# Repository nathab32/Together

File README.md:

# Together

## About

Together is a device for maintaining connections with friends and companions. Together is heavily inspired by Tamagotchi devices, but differs in that it is collaborative. Born from a graduating senior in need of grad gift ideas, Together hopes to allow friends to stay connected even after they are physically separated.

## Planned Features

- Record voice notes for friends or personal use
- Playback voice notes with integrated speaker
- Start streaks with your friends
- Addressible RGBs to see status of friends/do whatever you want
- Complete tasks with your companions to grow pets!
- Use as microphone for computer/phone or bluetooth speaker
- Tuner
- Metronome

ESP32-D0WD-V3

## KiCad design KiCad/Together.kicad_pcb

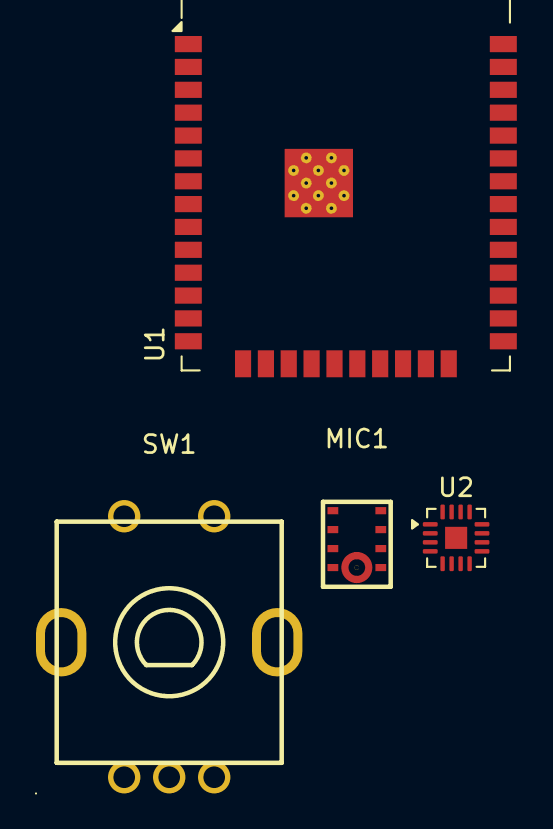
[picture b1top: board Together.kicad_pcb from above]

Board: 2 copper layers, 4 parts (0 on the bottom side), 3 nets, no tracks yet.

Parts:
MIC1: INMP441; MIC-SMD_INMP441
SW1: PEC11R-4220F-S0024; SW-TH_5P-L12.5-W13.4-P2.50-LS14.5-EH13.2
U1: ESP32-WROOM-32E; ESP32-WROOM-32D
U2: MAX98357A; TQFN-16-1EP_3x3mm_P0.5mm_EP1.23x1.23mm

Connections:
unnamed: U1.1 (GND), U1.15 (GND), U1.38 (GND), U1.39 (GND)
unnamed: U2.3 (GND), U2.11 (GND), U2.15 (GND)
unnamed: U2.7 (VDD), U2.8 (VDD)

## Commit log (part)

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2026-05-24 Create Audio class
2026-05-24 Add audio tools library
2026-05-25 Add A2DP library
2026-05-26 Remove incorrect lib dep and add partition
2026-05-27 Add credentials header file
2026-05-27 Ignore credentials header file
2026-05-27 fix missing function call
2026-05-27 Echo mic input through speaker
2026-06-01 Send messages to mqtt server
2026-06-03 remove a2dp library
2026-06-03 add mqtt library
2026-06-03 Send wav file to mqtt server
2026-06-09 Add examples commented out for easy access
2026-06-09 Add mic volume control, and change to pdm mic
2026-06-11 Send audio to server with button press
2026-06-11 write multiple wav files within a power cycle
